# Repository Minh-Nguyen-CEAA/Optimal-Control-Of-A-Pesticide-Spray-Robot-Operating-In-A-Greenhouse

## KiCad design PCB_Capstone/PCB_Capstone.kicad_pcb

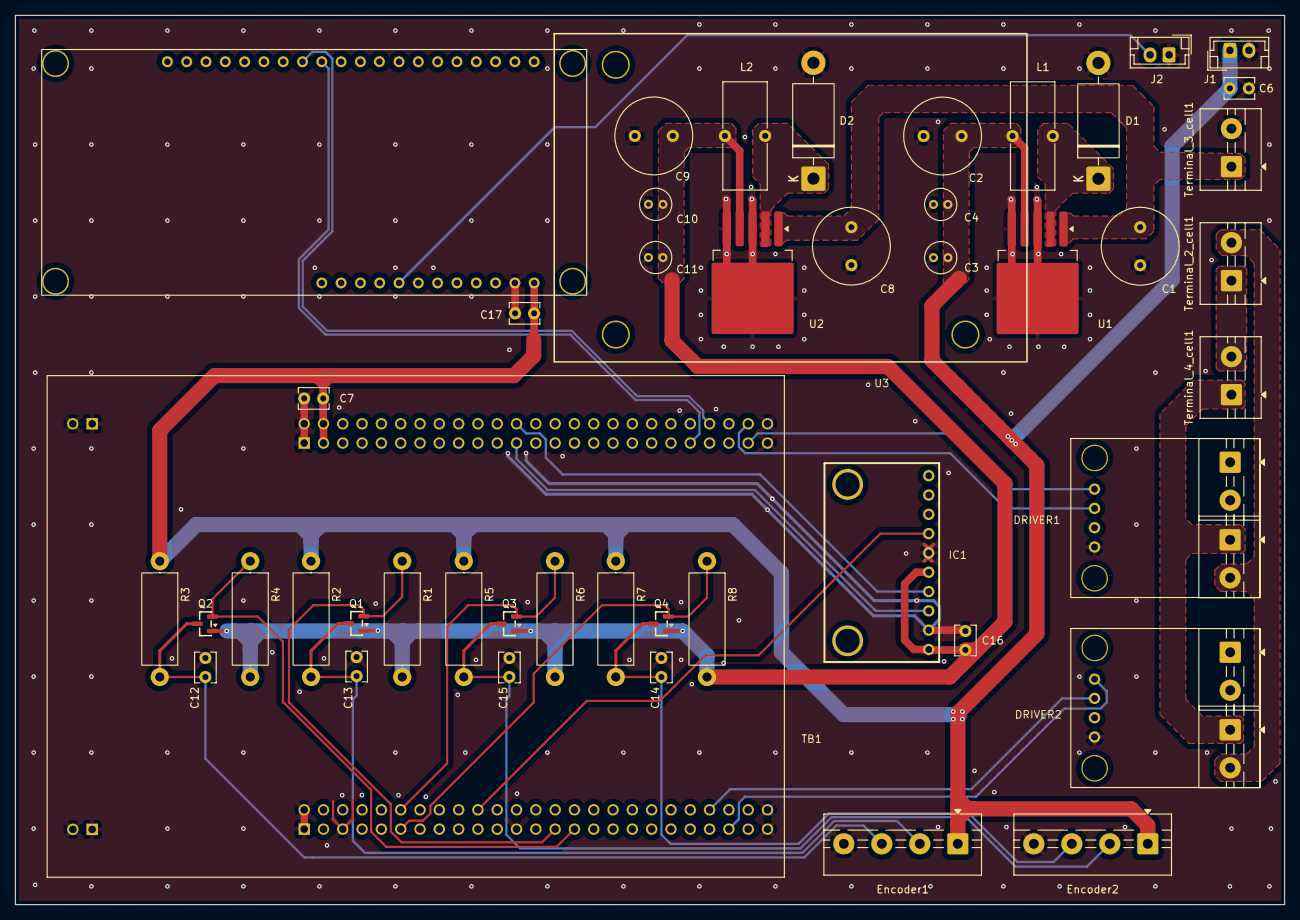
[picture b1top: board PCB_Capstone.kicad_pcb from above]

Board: 2 copper layers, 167.0 x 117.0 mm, 47 parts (0 on the bottom side), 27 nets.

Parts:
C1, C8: 100uF; C_Radial_D10.0mm_H20.0mm_P5.00mm
C2, C9: 220uF; C_Radial_D10.0mm_H12.5mm_P5.00mm
C3, C10: 10uF; C_Radial_D4.0mm_H7.0mm_P1.50mm
C4, C11: 0.1uF; C_Radial_D4.0mm_H7.0mm_P1.50mm
C6, C7, C16, C17: 0.1uF; C_Disc_D3.8mm_W2.6mm_P2.50mm
C12, C13, C14, C15: 1nF; C_Disc_D3.8mm_W2.6mm_P2.50mm
D1, D2: 1N5822; D_DO-201AD_P15.24mm_Horizontal
DRIVER1: MOTOR 1; Module Driver 8871
DRIVER2: MOTOR 2; Module Driver 8871
ESP32_UWB1: ESP32 UWB
Encoder1, Encoder2: Screw_Terminal_01x04; TerminalBlock_MaiXu_MX126-5.0-04P_1x04_P5.00mm
IC1: *; ICM-20948
J1, J2: Conn_01x02_Socket; JST_EH_B2B-EH-A_1x02_P2.50mm_Vertical
L1, L2: 33uH; L_Toroid_Vertical_L14.0mm_W5.6mm_P5.30mm_Bourns_5700
Q1, Q2, Q3, Q4: BSS138; SOT-23
R1, R2, R3, R4, R5, R6, R7, R8: 10K; R_Axial_DIN0414_L11.9mm_D4.5mm_P15.24mm_Horizontal
TB1: STM32F4DISCOVERY; STM32F411E-DISCO
Terminal_2_cell1, Terminal_3_cell1, Terminal_4_cell1: Screw_Terminal_01x02; TerminalBlock_MaiXu_MX126-5.0-02P_1x02_P5.00mm
U1: LM2596S-5; TO-263-5_TabPin3
U2: LM2596S-3.3; TO-263-5_TabPin3
U3: DWM

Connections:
+3.3V: C9.1, C10.1, C11.1, C16.2, IC1.1 (VCC), IC1.5 (NCS), L2.1, Q1.1 (G), Q2.1 (G), Q3.1 (G), Q4.1 (G), R1.2, R4.2, R6.2, R8.2, U2.4 (FB)
+5V: C2.1, C3.1, C4.1, C6.2, C7.2, C17.2, ESP32_UWB1.21 (5V0), Encoder1.1, Encoder2.1, J1.1, L1.1, R2.1, R3.1, R5.1, R7.1, TB1.P2_3 (5V), TB1.P2_4 (5V), U1.4 (FB)
+11.1V: C1.1, C8.1, Terminal_3_cell1.1 (+), U1.1 (VIN), U2.1 (VIN)
+24V: DRIVER1.7 (VM), DRIVER2.7 (VM), Terminal_4_cell1.1 (+)
/INT: IC1.7 (INT), TB1.P1_20 (PC4)
/RX: ESP32_UWB1.12 (IO25), TB1.P2_41 (PA10)
/SCL: IC1.3 (SCL), TB1.P2_23 (PB6)
/SDA: IC1.4 (SDA), TB1.P2_24 (PB7)
/Sig A_Encoder1: C13.1, Encoder1.2, Q1.3 (D), R2.2
/Sig A_Encoder2: C15.1, Encoder2.2, Q3.3 (D), R5.2
/Sig B_Encoder1: C12.1, Encoder1.3, Q2.3 (D), R3.2
/Sig B_Encoder2: C14.1, Encoder2.3, Q4.3 (D), R7.2
/TIM1_CH1: Q1.2 (S), R1.1, TB1.P1_27 (PE9)
/TIM1_CH2: Q2.2 (S), R4.1, TB1.P1_29 (PE11)
/TIM2_CH1: Q3.2 (S), R6.1, TB1.P1_12 (PA0-WKUP)
/TIM2_CH2: Q4.2 (S), R8.1, TB1.P1_11 (PA1)
/TIM3_CH1: DRIVER1.1 (IN2), TB1.P2_47 (PC6)
/TIM3_CH2: DRIVER1.2 (IN1), TB1.P2_48 (PC7)
/TIM4_CH1: DRIVER2.2 (IN1), TB1.P1_44 (PD12)
/TIM4_CH2: DRIVER2.1 (IN2), TB1.P1_45 (PD13)
/TX: ESP32_UWB1.13 (IO26), TB1.P2_44 (PA9)
/TX_RX UWB_ESP32: ESP32_UWB1.28 (IO16), J2.2
GND: C1.2, C2.2, C3.2, C4.2, C6.1, C7.1, C8.2, C9.2, C10.2, C11.2, C12.2, C13.2, C14.2, C15.2, C16.1, C17.1, D1.2 (A), D2.2 (A), DRIVER1.4 (GND), DRIVER2.4 (GND), ESP32_UWB1.22 (GND), Encoder1.4, Encoder2.4, IC1.2 (GND), IC1.6 (ADO), J1.2, J2.1, TB1.P1_1 (GND), TB1.P1_2 (GND), TB1.P1_5 (GND), TB1.P1_23 (GND), TB1.P1_49 (GND), TB1.P1_50 (GND), TB1.P2_1 (GND), TB1.P2_2 (GND), TB1.P2_49 (GND), TB1.P2_50 (GND), Terminal_3_cell1.2 (-), U1.3 (GND), U1.5 (~ON/OFF), U2.3 (GND), U2.5 (~ON/OFF)
GNDDC: DRIVER1.8 (GND), DRIVER2.8 (GND), Terminal_2_cell1.2 (-)
unnamed: D1.1 (K), L1.2, U1.2 (OUT)
unnamed: D2.1 (K), L2.2, U2.2 (OUT)
unnamed: Terminal_2_cell1.1 (+), Terminal_4_cell1.2 (-)
